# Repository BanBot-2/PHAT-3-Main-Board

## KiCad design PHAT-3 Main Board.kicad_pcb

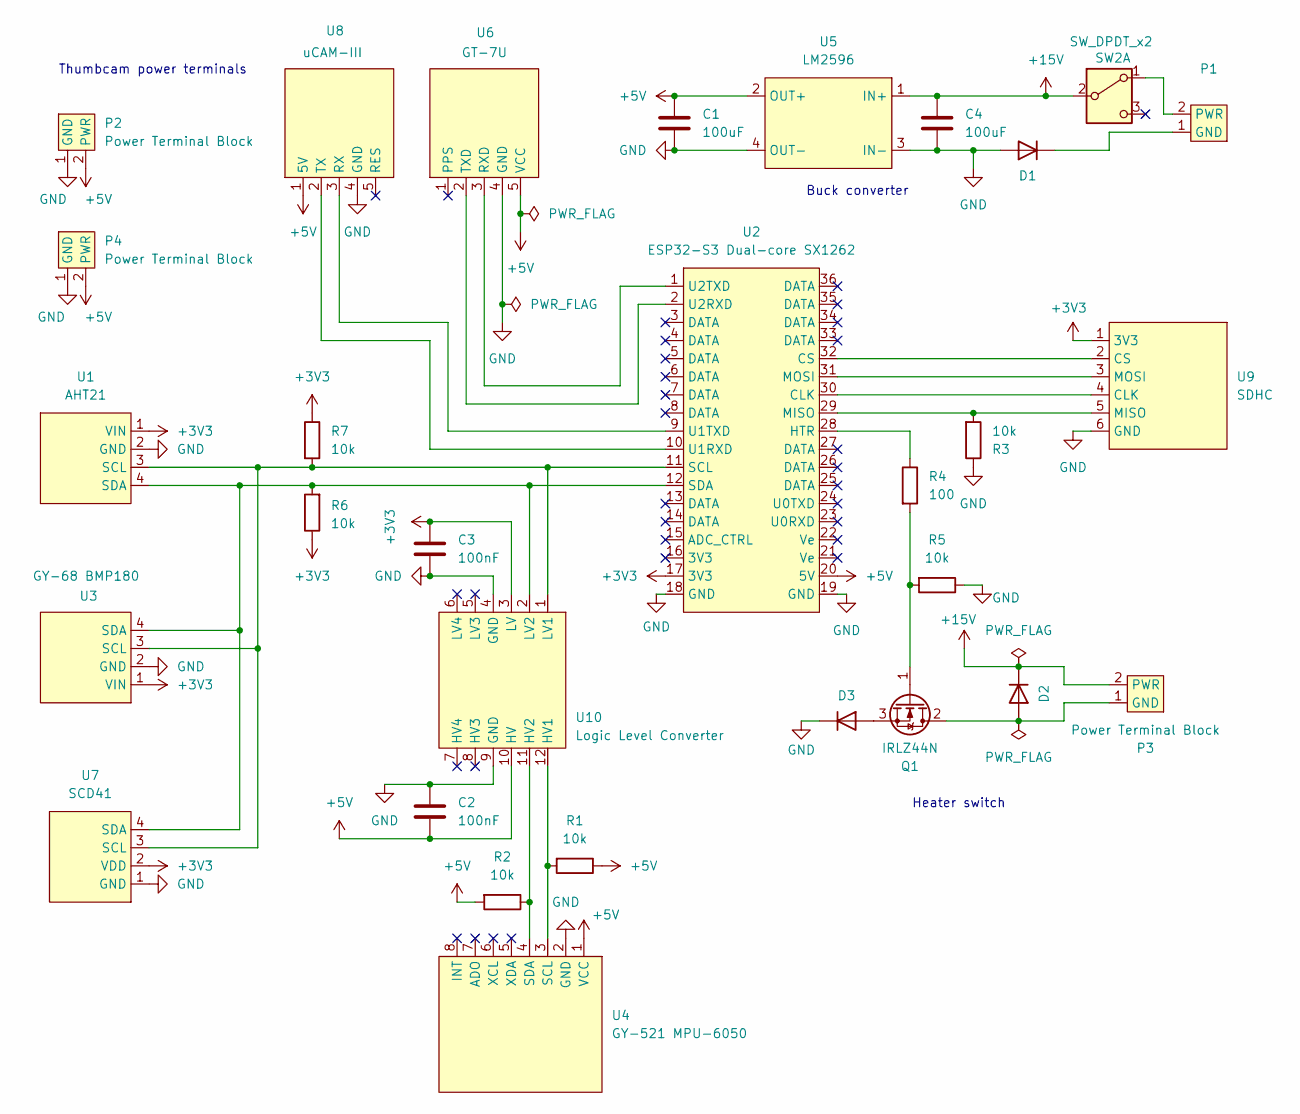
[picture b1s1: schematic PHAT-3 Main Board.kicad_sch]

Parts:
C1, C4: 100uF; C_Radial_D5.0mm_H11.0mm_P2.00mm
C2, C3: 100nF; C_Disc_D3.0mm_W2.0mm_P2.50mm
D1, D2, D3: D_DO-27_P12.70mm_Horizontal
P1, P2, P3, P4: Power Terminal Block; TerminalBlock_Phoenix_MKDS-1,5-2-5.08_1x02_P5.08mm_Horizont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
Q1: IRLZ44N; TO-220-3_Vertical
R1, R2, R3, R5, R6, R7: 10k; R_Axial_DIN0207_L6.3mm_D2.5mm_P10.16mm_Horizontal
R4: 100; R_Axial_DIN0207_L6.3mm_D2.5mm_P10.16mm_Horizontal
SW2: SW_DPDT_x2; SW_Slide-03_Wuerth-WS-SLTV_10x2.5x6.4_P2.54mm
U1: AHT21
U2: ESP32-S3 Dual-core SX1262
U3: GY-68 BMP180
U4: GY-521 MPU-6050
U5: LM2596
U6: GT-7U; GT-U7
U7: SCD41
U8: uCAM-III
U9: SDHC
U10: Logic Level Converter

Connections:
+3V3: C3.1, R6.1, R7.1, U1.1 (VIN), U2.17 (3V3), U3.1 (VIN), U7.2 (VDD), U9.1 (3V3), U10.3 (LV)
+5V: C1.1, C2.2, P2.2 (PWR), P4.2 (PWR), R1.1, R2.2, U2.20 (5V), U4.1 (VCC), U5.2 (OUT+), U6.5 (VCC), U8.1 (5V), U10.10 (HV)
+15V: C4.1, D2.1 (K), P3.2 (PWR), SW2.2 (B), U5.1 (IN+)
GND: C1.2, C2.1, C3.2, C4.2, D1.2 (A), D3.1 (K), P2.1 (GND), P4.1 (GND), R3.1, R5.1, U1.2 (GND), U2.18 (GND), U2.19 (GND), U3.2 (GND), U4.2 (GND), U5.3 (IN-), U5.4 (OUT-), U6.4 (GND), U7.1 (GND), U8.4 (GND), U9.6 (GND), U10.4 (GND), U10.9 (GND)
unnamed: D1.1 (K), P1.1 (GND)
unnamed: D2.2 (A), P3.1 (GND), Q1.2 (D)
unnamed: D3.2 (A), Q1.3 (S)
unnamed: P1.2 (PWR), SW2.1 (A)
unnamed: Q1.1 (G), R4.2, R5.2
unnamed: R7.2, U1.3 (SCL), U2.11 (SCL), U3.3 (SCL), U7.3 (SCL), U10.1 (LV1)
unnamed: R6.2, U1.4 (SDA), U2.12 (SDA), U3.4 (SDA), U7.4 (SDA), U10.2 (LV2)
unnamed: U2.30 (CLK), U9.4 (CLK)
unnamed: U2.32 (CS), U9.2 (CS)
unnamed: R4.1, U2.28 (HTR)
unnamed: R3.2, U2.29 (MISO), U9.5 (MISO)
unnamed: U2.31 (MOSI), U9.3 (MOSI)
unnamed: U2.10 (U1RXD), U8.2 (TX)
unnamed: U2.9 (U1TXD), U8.3 (RX)
unnamed: U2.2 (U2RXD), U6.2 (TXD)
unnamed: U2.1 (U2TXD), U6.3 (RXD)
unnamed: R1.2, U4.3 (SCL), U10.12 (HV1)
unnamed: R2.1, U4.4 (SDA), U10.11 (HV2)

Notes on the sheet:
Heater switch
Thumbcam power terminals
Buck converter

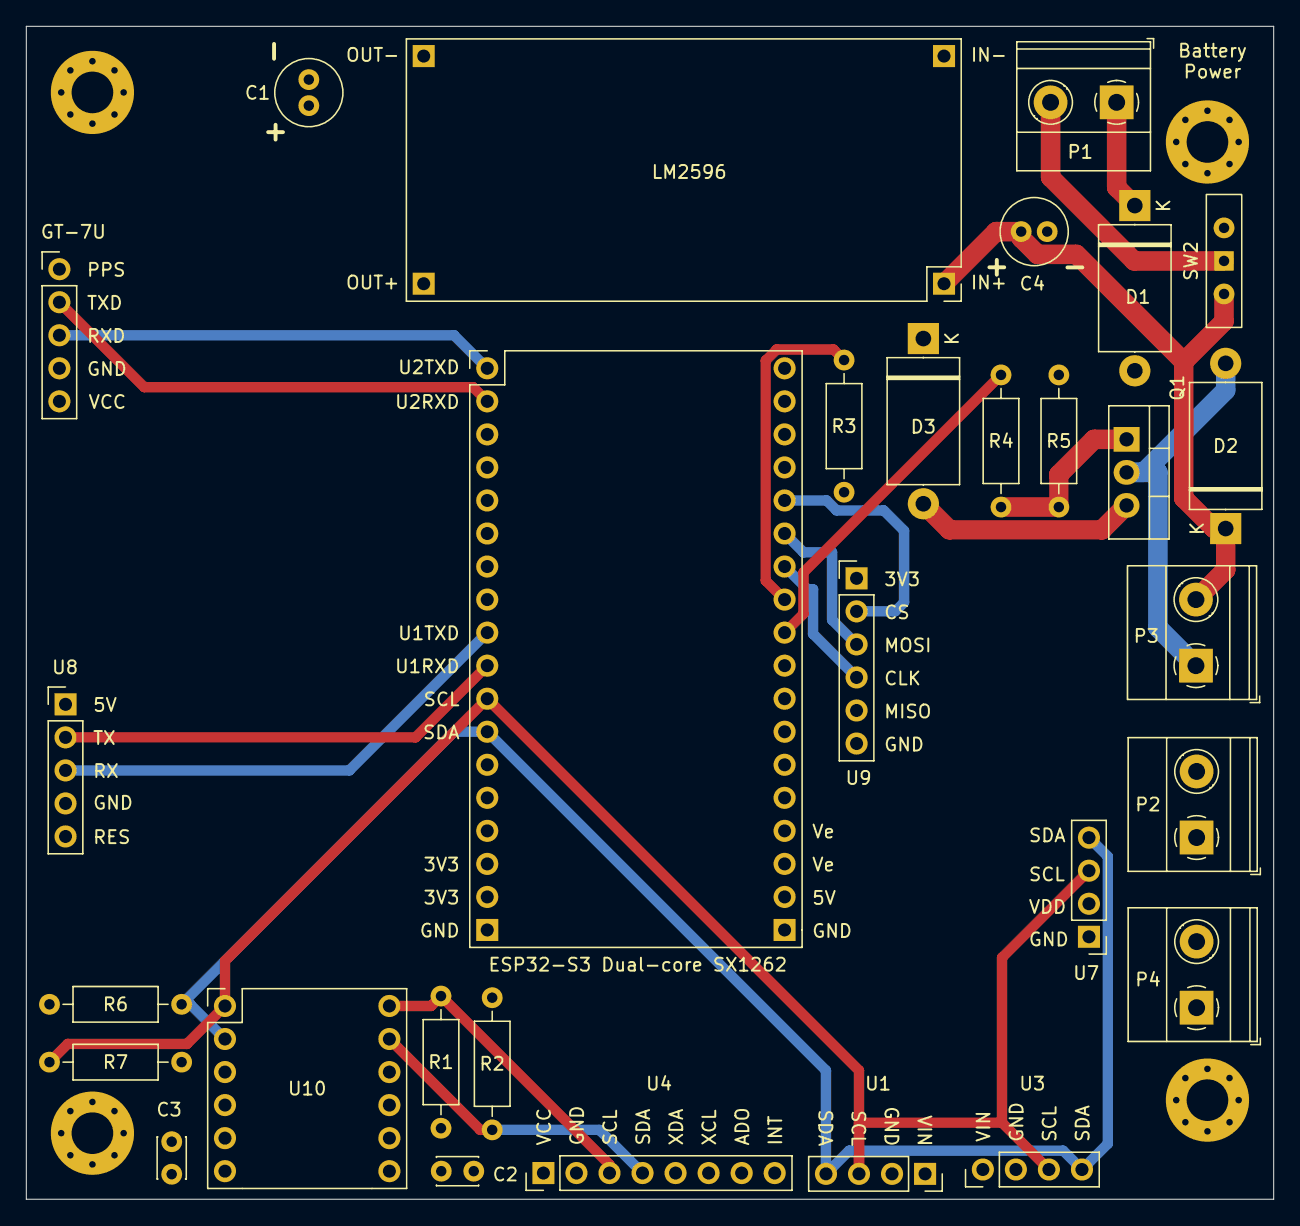
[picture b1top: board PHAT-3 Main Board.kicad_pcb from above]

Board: 6 copper layers, 95.9 x 90.2 mm, 30 parts (0 on the bottom side), 22 nets.

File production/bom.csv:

Designator,Footprint,Quantity,Value,LCSC Part #
"C1, C4",C_Radial_D5.0mm_H11.0mm_P2.00mm,2,100uF,
"C2, C3",C_Disc_D3.0mm_W2.0mm_P2.50mm,2,100nF,
"D1, D2, D3",D_DO-27_P12.70mm_Horizontal,3,~,
"P1, P2, P3, P4","TerminalBlock_Phoenix_MKDS-1,5-2-5.08_1x02_P5.08mm_Horizontal",4,Power Terminal Block,
Q1,TO-220-3_Vertical,1,IRLZ44N,
"R1, R2, R3, R5, R6, R7",R_Axial_DIN0207_L6.3mm_D2.5mm_P10.16mm_Horizontal,6,10k,
R4,R_Axial_DIN0207_L6.3mm_D2.5mm_P10.16mm_Horizontal,1,100,
SW2,SW_Slide-03_Wuerth-WS-SLTV_10x2.5x6.4_P2.54mm,1,SW_DPDT_x2,
U1,AHT21,1,AHT21,
U10,Logic Level Converter,1,Logic Level Converter,
U2,ESP32-S3 Dual-core SX1262,1,ESP32-S3 Dual-core SX1262,
U3,GY-68 BMP180,1,GY-68 BMP180,
U4,GY-521 MPU-6050,1,GY-521 MPU-6050,
U5,LM2596,1,LM2596,
U6,GT-U7,1,GT-7U,
U7,SCD41,1,SCD41,
U8,uCAM-III,1,uCAM-III,
U9,SDHC,1,SDHC,

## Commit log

2025-01-17 Initial commit
    Blank KiCAD file.
2025-01-18 One sensor and main board
    Added the BMP180 and our main LoRa radio board
2025-01-18 Forgot to save cache
2025-01-18 Added AHT21 I2C IIC
2025-01-21 Added Buck Converter and Rest of Sensors
2025-01-22 Updated Silk Screens
2025-01-23 Updated GY-BMP180 to BME280
2025-01-24 Updated LM2596 Footprint Size
2025-01-25 Updated Footprint Sizes and Started Adding uCAM-III
2025-01-26 Finished Adding uCAM-III
2025-01-27 Added SD Card Reader
2025-01-29 Added logic Level Converter and Relay
2025-01-29 Tried Wiring Everything
2025-02-01 First Wiring Draft
2025-02-01 Finished Wiring and Implemented MOSFET
2025-02-02 Rewired Everything Again
2025-02-02 Updated Footprint Sizes and SD Card Reader
2025-02-03 Made a Preliminary PCB Layout
2025-02-03 Redid PCB Arrangement
2025-02-04 Tweaked Silk Screens and Gave Sensors More Room
2025-02-11 Added Diodes and Switch
2025-02-11 Updated Switch and Resistor Placement
2025-02-12 Changed UART and I2C Pins
2025-02-13 Routed the PCB.
2025-02-16 Final touches! :)
2025-02-16 Final revision FINAL_FINAL_2
